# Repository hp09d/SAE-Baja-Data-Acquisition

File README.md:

# SAE-Baja-Data-Acquisition
Senior Design project year 2014-2015

See the [To Do List](../../wiki/To-Do) and the rest of the [Project Wiki](../../wiki/) for more information

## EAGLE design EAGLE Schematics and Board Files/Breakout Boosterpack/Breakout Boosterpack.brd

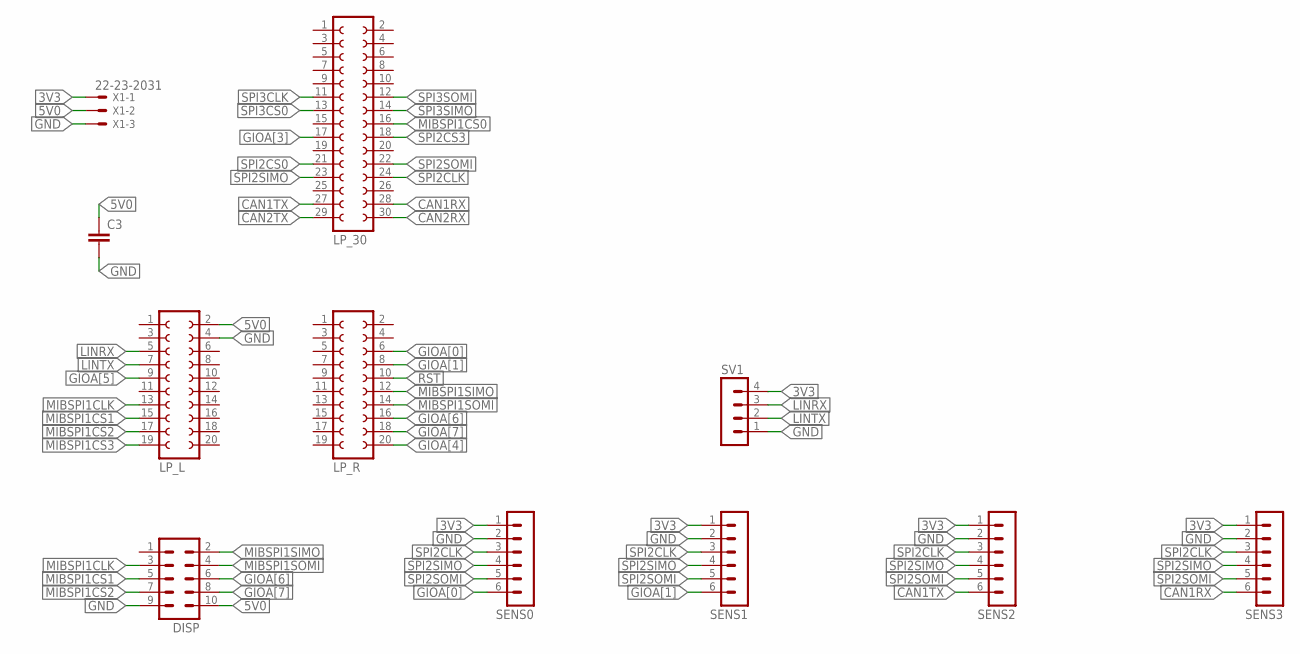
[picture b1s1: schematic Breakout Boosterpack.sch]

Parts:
C3: C2.5/5; C2.5-5
DISP: MA05-2
LP_30: FE15-2
LP_L: FE10-2
LP_R: FE10-2
SENS0, SENS1, SENS2, SENS3: MA06-1
SV1: MA04-1
X1: 22-23-2031

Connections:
3V3: SENS0.1, SENS1.1, SENS2.1, SENS3.1, SV1.4, X1.1
5V0: C3.1, DISP.10, LP_L.2, X1.2
CAN1RX: LP_30.28, SENS3.6
CAN1TX: LP_30.27, SENS2.6
CAN2RX: LP_30.30
CAN2TX: LP_30.29
GIOA[0]: LP_R.6, SENS0.6
GIOA[1]: LP_R.8, SENS1.6
GIOA[3]: LP_30.17
GIOA[4]: LP_R.20
GIOA[5]: LP_L.9
GIOA[6]: DISP.6, LP_R.16
GIOA[7]: DISP.8, LP_R.18
GND: C3.2, DISP.9, LP_L.4, SENS0.2, SENS1.2, SENS2.2, SENS3.2, SV1.1, X1.3
LINRX: LP_L.5, SV1.3
LINTX: LP_L.7, SV1.2
MIBSPI1CLK: DISP.3, LP_L.13
MIBSPI1CS0: LP_30.16
MIBSPI1CS1: DISP.5, LP_L.15
MIBSPI1CS2: DISP.7, LP_L.17
MIBSPI1CS3: LP_L.19
MIBSPI1SIMO: DISP.2, LP_R.12
MIBSPI1SOMI: DISP.4, LP_R.14
RST: LP_R.10
SPI2CLK: LP_30.24, SENS0.3, SENS1.3, SENS2.3, SENS3.3
SPI2CS0: LP_30.21
SPI2CS3: LP_30.18
SPI2SIMO: LP_30.23, SENS0.4, SENS1.4, SENS2.4, SENS3.4
SPI2SOMI: LP_30.22, SENS0.5, SENS1.5, SENS2.5, SENS3.5
SPI3CLK: LP_30.11
SPI3CS0: LP_30.13
SPI3SIMO: LP_30.14
SPI3SOMI: LP_30.12

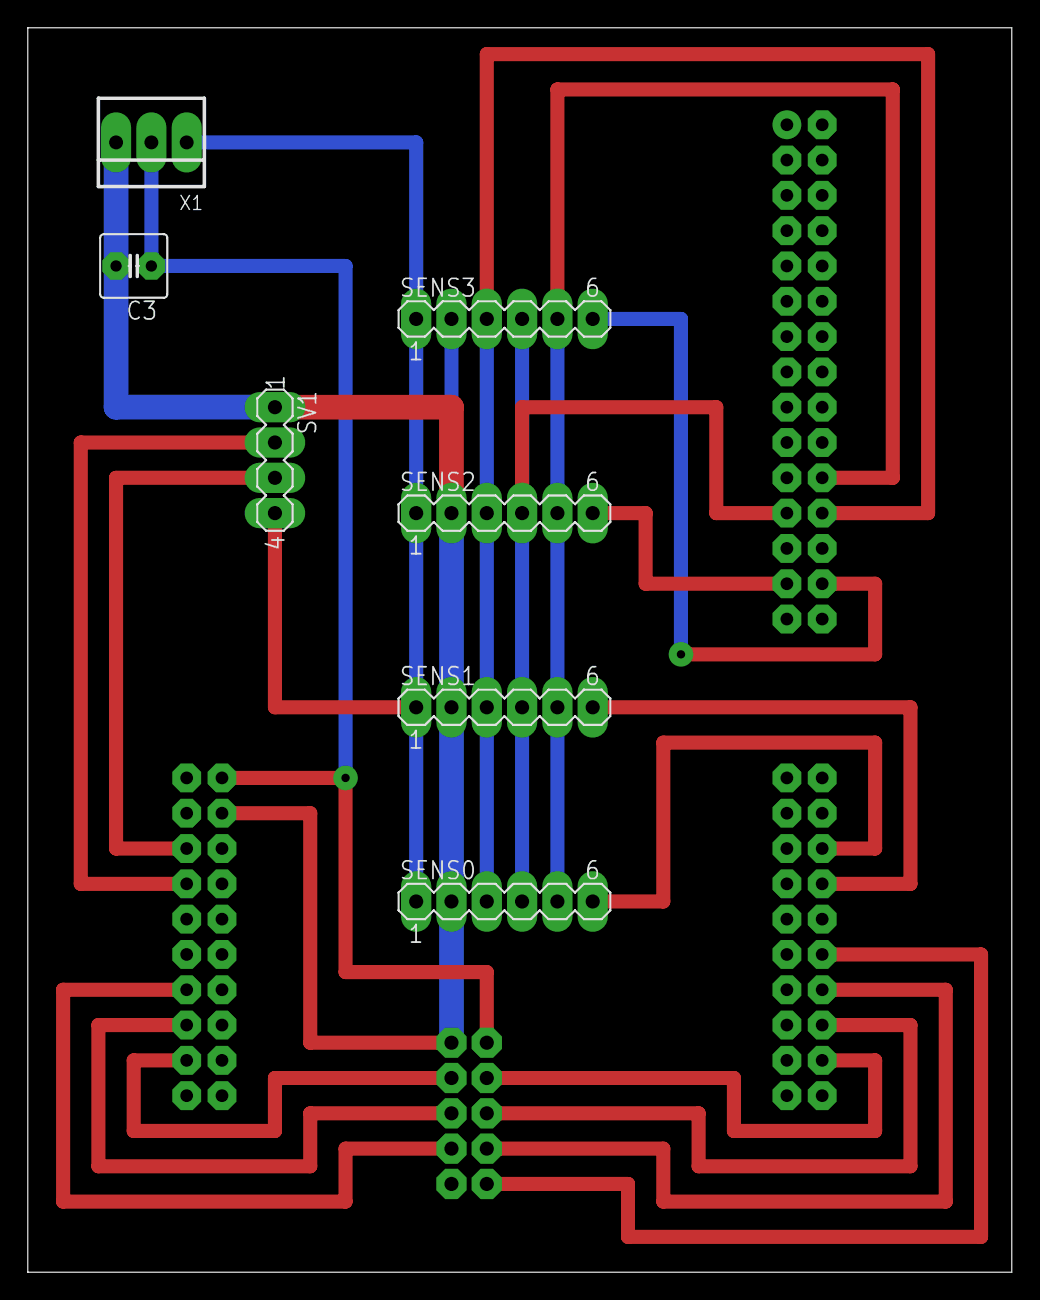
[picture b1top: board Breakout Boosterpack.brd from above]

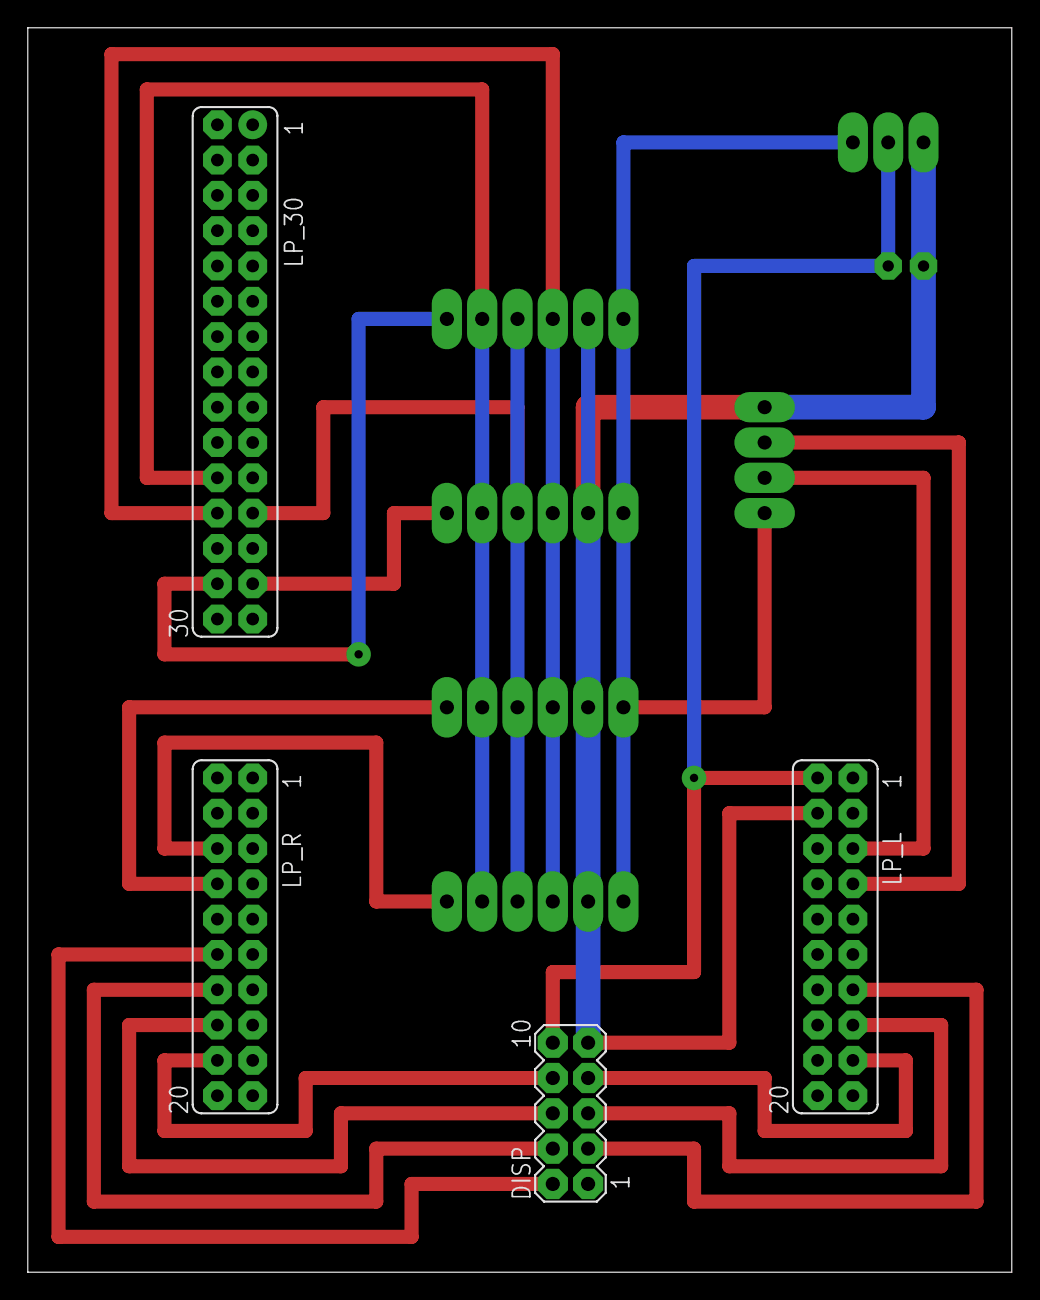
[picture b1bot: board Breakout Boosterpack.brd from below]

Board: 2 copper layers, 70.8 x 89.5 mm, 11 parts (4 on the bottom side), 19 nets.

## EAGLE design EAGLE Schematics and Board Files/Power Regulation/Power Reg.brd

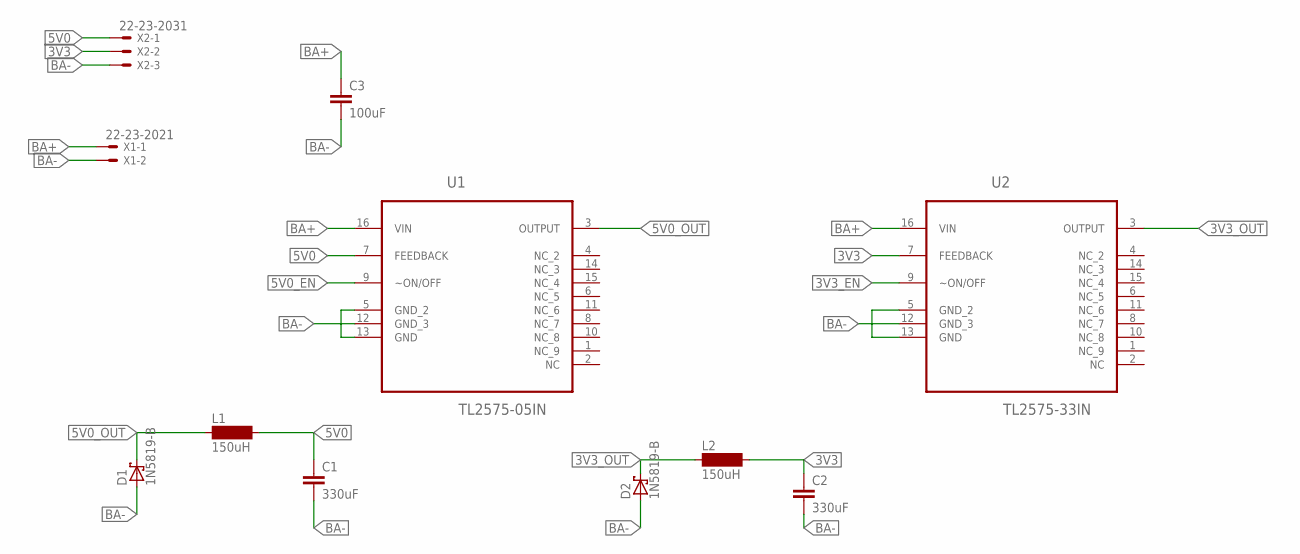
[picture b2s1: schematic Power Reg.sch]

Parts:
C1, C2: 330uF; C5B3.5
C3: 100uF; C5B3.5
D1, D2: 1N5819-B; DO41-7.6
L1, L2: 150uH; SD8
U1: TL2575-05IN; DIP254P762X508-16
U2: TL2575-33IN; DIP254P762X508-16
X1: 22-23-2021
X2: 22-23-2031

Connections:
3V3: C2.1, L2.2, U2.7 (FEEDBACK), X2.2
3V3_EN: U2.9 (~ON/OFF)
3V3_OUT: D2.C, L2.1, U2.3 (OUTPUT)
5V0: C1.1, L1.2, U1.7 (FEEDBACK), X2.1
5V0_EN: U1.9 (~ON/OFF)
5V0_OUT: D1.C, L1.1, U1.3 (OUTPUT)
BA+: C3.1, U1.16 (VIN), U2.16 (VIN), X1.1
BA-: C1.2, C2.2, C3.2, D1.A, D2.A, U1.5 (GND_2), U1.12 (GND_3), U1.13 (GND), U2.5 (GND_2), U2.12 (GND_3), U2.13 (GND), X1.2, X2.3

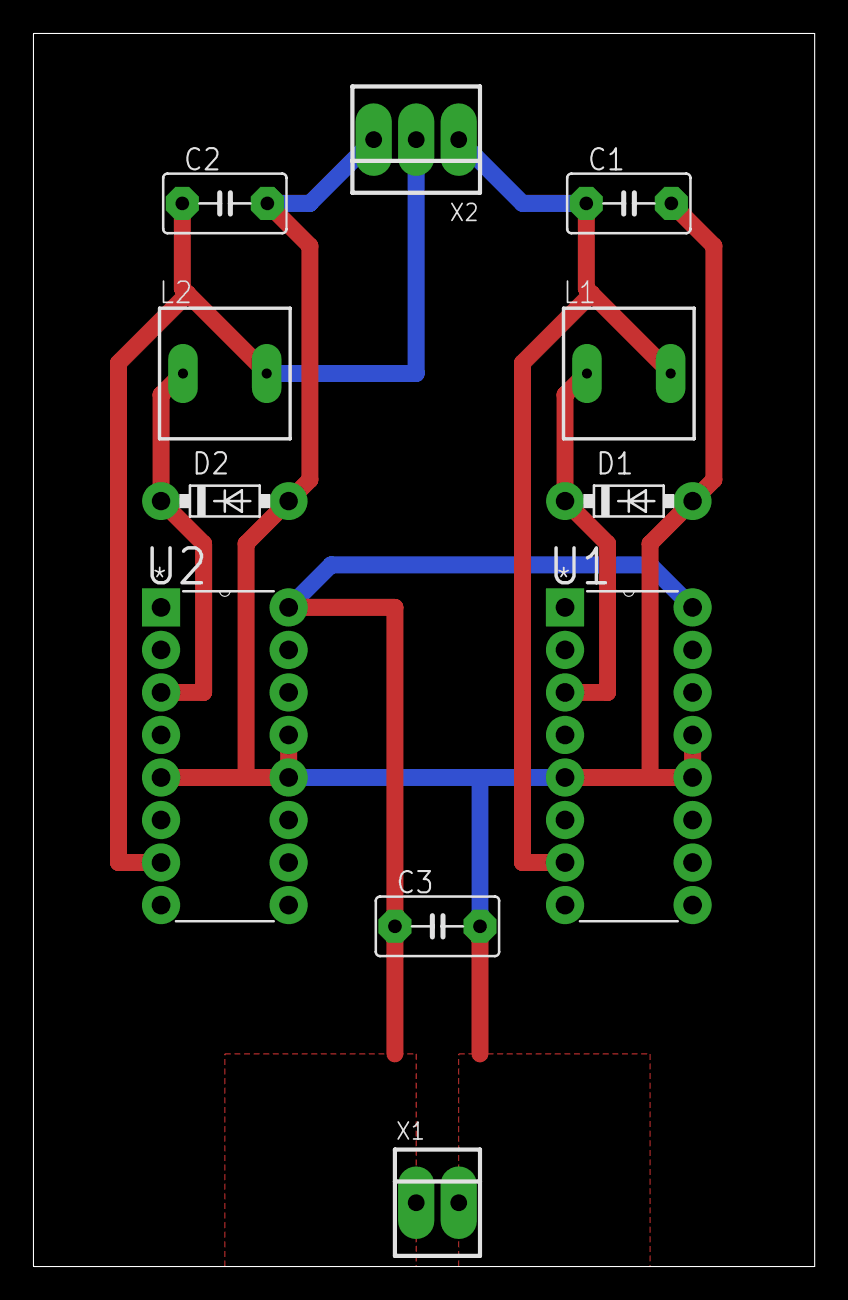
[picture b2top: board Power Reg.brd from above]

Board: 2 copper layers, 46.7 x 73.7 mm, 11 parts (0 on the bottom side), 6 nets.

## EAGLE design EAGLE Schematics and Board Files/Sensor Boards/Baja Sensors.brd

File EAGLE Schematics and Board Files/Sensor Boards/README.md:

This board design is based around the MSP430G2553IN20. It includes a stabilizing RC pair on the reset pin, as well as an optional reset button.

This board is used as a platform for building sensor modules for the Baja car. It breaks out power, ground, and both serial interfaces (UCA and UCB), as well as analog pins 0-2, 4, and 5.
The pinout of the UCB header matches with pins 2-7 of the UCA/ANALOG header for easily switching interfaces.

UCB Header:

|Pin #|MSP430 Pin|Primary Function|Secondary Function|
|-------|--------|----------------|------------------|
|1|VCC|3V3||
|2|P1.6|UCB0SOMI|UCB0SCL|
|3|P1.7|UCB0SIMO|UCB0SDA|
|4|P1.5|UCB0CLK|UCA0STE|
|5|P1.4|UCB0STE|UCA0CLK|
|6|VSS|GND||

UCA/ANALOG Header:

|Pin #|MSP430 Pin|Primary Function|Secondary Function|
|-----|----------|----------------|------------------|
|1|P1.0|A0||
|2|DVCC|3V3||
|3|P1.1|A1|UCA0SOMI|
|4|P1.2|A2|UCA0SIMO|
|5|P1.4|UCA0CLK|UCB0STE|
|6|P1.5|UCA0STE|UCB0CLK|
|7|DVSS|GND||

Note that UCA or analog must be selected internally.

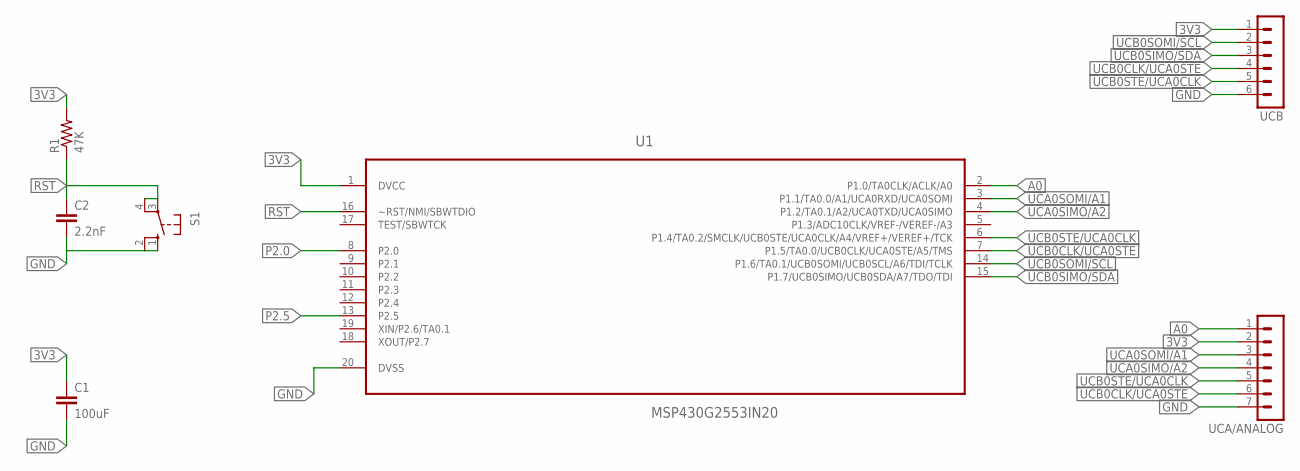
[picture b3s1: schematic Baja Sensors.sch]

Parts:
C1: 100uF; C5B5
C2: 2.2nF; C5B3
R1: 47K; 0207/5V
S1: 10-XX; B3F-10XX
U1: MSP430G2553IN20; DIP254P762X508-20
UCA/ANALOG: MA07-1
UCB: MA06-1

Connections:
3V3: C1.1, R1.2, U1.1 (DVCC), UCA/ANALOG.2, UCB.1
A0: U1.2 (P1.0/TA0CLK/ACLK/A0), UCA/ANALOG.1
GND: C1.2, C2.2, S1.1 (S), S1.2 (S1), U1.20 (DVSS), UCA/ANALOG.7, UCB.6
P2.0: U1.8 (P2.0)
P2.5: U1.13 (P2.5)
RST: C2.1, R1.1, S1.3, S1.4 (P1), U1.16 (~RST/NMI/SBWTDIO)
UCA0SIMO/A2: U1.4 (P1.2/TA0.1/A2/UCA0TXD/UCA0SIMO), UCA/ANALOG.4
UCA0SOMI/A1: U1.3 (P1.1/TA0.0/A1/UCA0RXD/UCA0SOMI), UCA/ANALOG.3
UCB0CLK/UCA0STE: U1.7 (P1.5/TA0.0/UCB0CLK/UCA0STE/A5/TMS), UCA/ANALOG.6, UCB.4
UCB0SIMO/SDA: U1.15 (P1.7/UCB0SIMO/UCB0SDA/A7/TDO/TDI), UCB.3
UCB0SOMI/SCL: U1.14 (P1.6/TA0.1/UCB0SOMI/UCB0SCL/A6/TDI/TCLK), UCB.2
UCB0STE/UCA0CLK: U1.6 (P1.4/TA0.2/SMCLK/UCB0STE/UCA0CLK/A4/VRE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), UCA/ANALOG.5, UCB.5

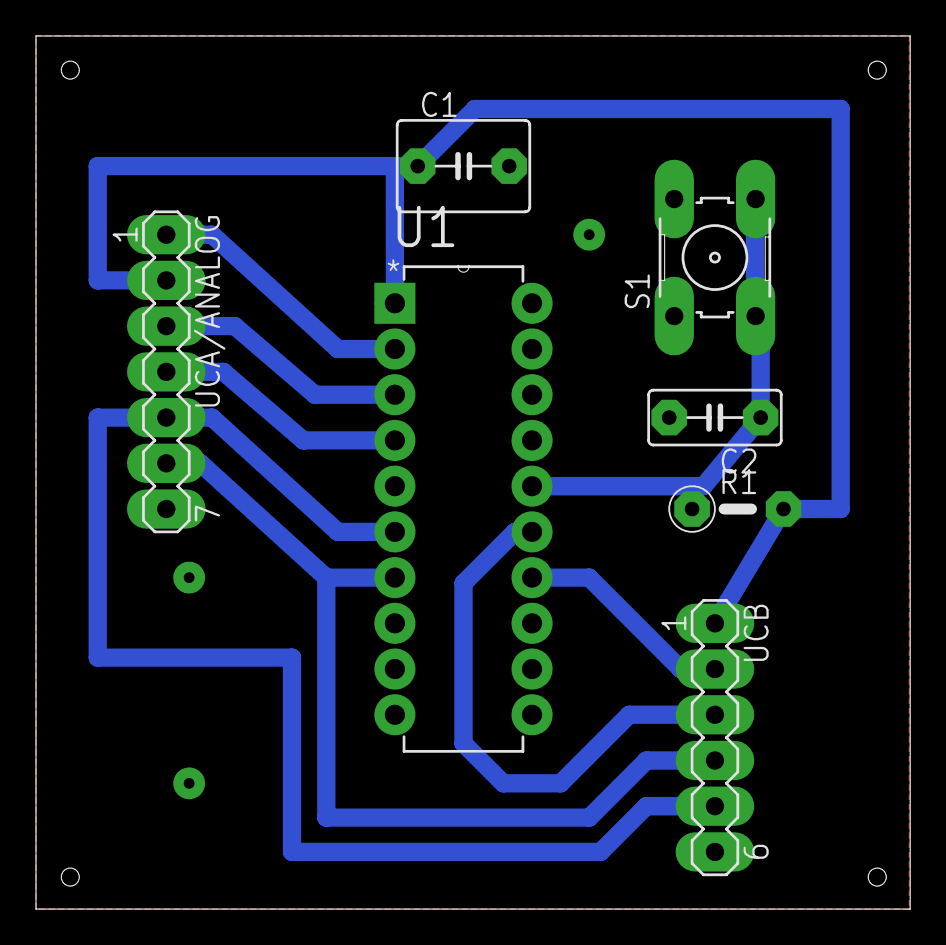
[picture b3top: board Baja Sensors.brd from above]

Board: 2 copper layers, 48.6 x 48.5 mm, 7 parts (0 on the bottom side), 10 nets.

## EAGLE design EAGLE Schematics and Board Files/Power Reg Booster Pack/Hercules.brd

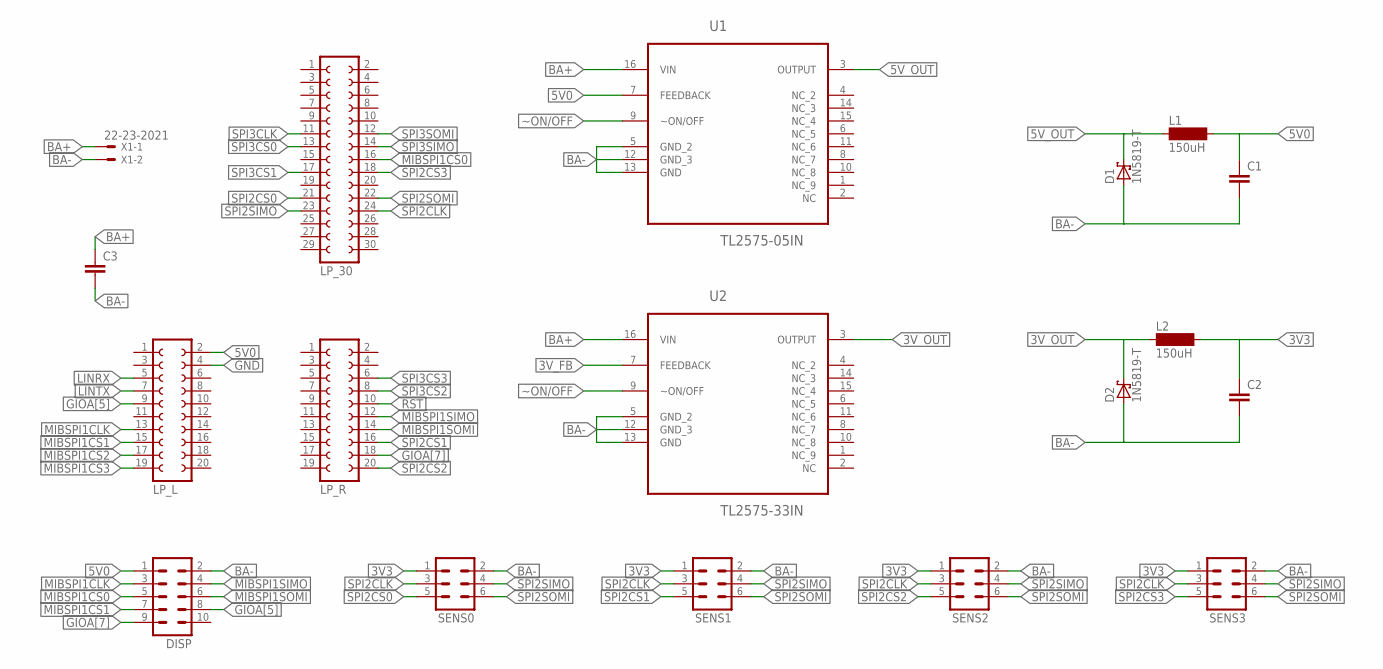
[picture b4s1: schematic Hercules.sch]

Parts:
C1, C2: C7.5/6; C7.5B6
C3: C2.5/5; C2.5-5
D1, D2: 1N5819-T; DO41-7.6
DISP: MA05-2
L1, L2: 150uH; BS75
LP_30: FE15-2
LP_L: FE10-2
LP_R: FE10-2
SENS0, SENS1, SENS2, SENS3: MA03-2
U1: TL2575-05IN; DIP254P762X508-16
U2: TL2575-33IN; DIP254P762X508-16
X1: 22-23-2021

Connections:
3V3: C2.1, L2.2, SENS0.1, SENS1.1, SENS2.1, SENS3.1
3V_FB: U2.7 (FEEDBACK)
3V_OUT: D2.C, L2.1, U2.3 (OUTPUT)
5V0: C1.1, DISP.1, L1.2, LP_L.2, U1.7 (FEEDBACK)
5V_OUT: D1.C, L1.1, U1.3 (OUTPUT)
BA+: C3.1, U1.16 (VIN), U2.16 (VIN), X1.1
BA-: C1.2, C2.2, C3.2, D1.A, D2.A, DISP.2, SENS0.2, SENS1.2, SENS2.2, SENS3.2, U1.5 (GND_2), U1.12 (GND_3), U1.13 (GND), U2.5 (GND_2), U2.12 (GND_3), U2.13 (GND), X1.2
GIOA[5]: DISP.8, LP_L.9
GIOA[7]: DISP.9, LP_R.18
GND: LP_L.4
LINRX: LP_L.5
LINTX: LP_L.7
MIBSPI1CLK: DISP.3, LP_L.13
MIBSPI1CS0: DISP.5, LP_30.16
MIBSPI1CS1: DISP.7, LP_L.15
MIBSPI1CS2: LP_L.17
MIBSPI1CS3: LP_L.19
MIBSPI1SIMO: DISP.4, LP_R.12
MIBSPI1SOMI: DISP.6, LP_R.14
RST: LP_R.10
SPI2CLK: LP_30.24, SENS0.3, SENS1.3, SENS2.3, SENS3.3
SPI2CS0: LP_30.21, SENS0.5
SPI2CS1: LP_R.16, SENS1.5
SPI2CS2: LP_R.20, SENS2.5
SPI2CS3: LP_30.18, SENS3.5
SPI2SIMO: LP_30.23, SENS0.4, SENS1.4, SENS2.4, SENS3.4
SPI2SOMI: LP_30.22, SENS0.6, SENS1.6, SENS2.6, SENS3.6
SPI3CLK: LP_30.11
SPI3CS0: LP_30.13
SPI3CS1: LP_30.17
SPI3CS2: LP_R.8
SPI3CS3: LP_R.6
SPI3SIMO: LP_30.14
SPI3SOMI: LP_30.12
~ON/OFF: U1.9 (~ON/OFF), U2.9 (~ON/OFF)

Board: 2 copper layers, 18 parts (3 on the bottom side), 21 nets, no tracks yet.

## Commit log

2015-01-14 Added some folders and an empty file
2015-01-14 Hercules TFT Example
    Cute puppy example using mibSPI on the TMS570LS0432
2015-01-14 Revert "Hercules TFT Example"
    This reverts commit 969f1ae5e69e2b7a980252e8d62cb8c3055a23b0.
2015-01-14 Hercules TFT Display Example
    Cute puppy BMP drawing example for using mibSPI on the TMS570LS0432
2015-01-15 Hercules TFT Display Library
2015-01-22 Updated Display Library
    Added a 9x8 font and string print support
2015-01-24 UART on the Raspberry Pi
    Quick example that sends a message and prints responses to stdout.
2015-01-24 MSP430 SPI Example
    Sends SLV_data to the master when the STE line is pulled low. SLV_data
    is incremented after each transmission.
2015-01-25 Sensor Board Schematics
    Preliminary board design. Breaks out USCA and USCB, as well as analog
    pins 0-2. Includes an optional status LED on P2.0 and reset button.
2015-01-25 Revert "Sensor Board Schematics"
    This reverts commit 3a7d3a997371d78742c907e4d318bd2ab598de01.
2015-01-25 Sensor Board Schematics
    Preliminary sensor board designs - pending information from Dante about
    PCB milling tolerances.
    Includes optional reset button and status LED
2015-01-25 EAGLE Library
    Some components used on the project
2015-01-26 Hercules Booster Pack
    Power regulation and interface breakout
2015-02-04 Start of Hercules UART
2015-02-05 Update MSP430G2553_SPI_Slave.c
    added a comment for later use
2015-02-06 Hercules SPI1 (Legacy) Master Mode Test
2015-02-06 Revert "Hercules SPI1 (Legacy) Master Mode Test"
    This reverts commit c64262679a3adc7487932799ebad8c771b1ec224.
2015-02-09 Hercules SDHC Baseline Test
    Reads the partition table and finds the first FAT partition
2015-02-09 Hercules SDHC Baseline Test
    Reads the partition table, first MBR, and the root of the file system
2015-02-13 Update MSP430G2553_SPI_Slave.c
    Added sample code for 2-byte transmission
2015-02-13 Update MSP430G2553_SPI_Slave.c
    Removed redundant code
2015-02-13 Update MSP430G2553_SPI_Slave.c
    changed stuff
2015-02-18 Hercules sending messages through UART complete
2015-02-22 Hercules FatFS SD Card Read/Write
    FatFS port for TMS570LS04x. Writing doesn't work 100% yet and init is
    very hit or miss.
2015-02-22 Fixed WDT
    Pulled WDT disable out of SPI_Init so that it runs even if SPI_Init is
    not.
2015-02-22 Hercules FatFS SD Card Read/Write
    Working code to read and write to files on an SDHC card. Maybe a little
    touchy, may need some reworking.
2015-02-22 Hall effect module counts rotations
2015-02-23 FatFS SDHC w/ ILI9340 Test
2015-02-23 Example
2015-02-23 Updated FatFS Port
    Uses mibSPI instead of legacy
2015-02-24 LSM303 I2C
    Initial commit
2015-02-24 Reads the timer register and attempts to calculate RPM. Has trouble for decimal values under one. Probly an unsigned int thing.
2015-02-26 counts time between rotations and calculates RPM
2015-02-27 w/ SPI
2015-03-01 From Hardware/Software Demo 2/27/2015
2015-03-01 Folder Cleanup
2015-03-04 New sensor board design & Gerber files
2015-03-10 Single byte SPI
    Code used to program MSP430s on demo day
2015-03-17 Updated Sensor Board Drill Hole Dimensions
2015-03-17 Removed Power Reg Booster Pack Files
    Cannot be milled in-house, must be redesigned.
2015-03-22 Hercules Demo HalcoGen Files
2015-03-22 Updated Sensor Board Schematic & Gerber Files
2015-03-23 Updated ILI9340 Display Library
2015-03-23 Entire Hercules Demo Project Code
2015-03-23 Power Regulator PCB
2015-03-23 LSM303 I2C
    Bit-banged I2C. Multi-byte SPI working.
2015-03-24 Updated PCBs
    Increased pad size
2015-03-24 Hercules Demo Code
    Most up to date
2015-03-27 Actually made it detect edges
2015-03-29 Hercules Code For Auburn Event
    New XBee frame structure and more
2015-03-29 New RasPi GUI
2015-03-29 FatFS Update
    Added some error handling
2015-04-01 Hercules Booster Pack PCB
2015-04-01 Some changes
    WIP
2015-04-03 MSP430 Hall Effect Sensor Code
    Should be complete. Calculates speed in MPH and stores as a UQ6.2
    fixed-point number. Uses a single-byte SPI transfer (interrupts to be
    removed).
    Changes to original code:
    - Tightened up the detection of the pulses from the ADC values.
    Increased from 450 - 700.
2015-04-03 Added comments & Removed unnecessary code
    Commented code and removed some unnecessary things that were left in
2015-04-03 Added uncommitted files
    A few minor changes to the design paradigm. Has been done for a while,
    just forgot to commit.
2015-04-04 Optimizations
    Tested and works. Unsure if speed is accurate. Removed some unnecessary
    floating point operations, cycle delays, and the SPI interrupts.
2015-04-04 Added clock setup
    elegance
2015-04-20 Final Hercules Code
    Hercules code run in auburn, before it went to shit
2015-04-20 Cleanup
2015-04-20 Extras
2015-04-20 Added 2-axis Function
    Reads only x and y axis registers
